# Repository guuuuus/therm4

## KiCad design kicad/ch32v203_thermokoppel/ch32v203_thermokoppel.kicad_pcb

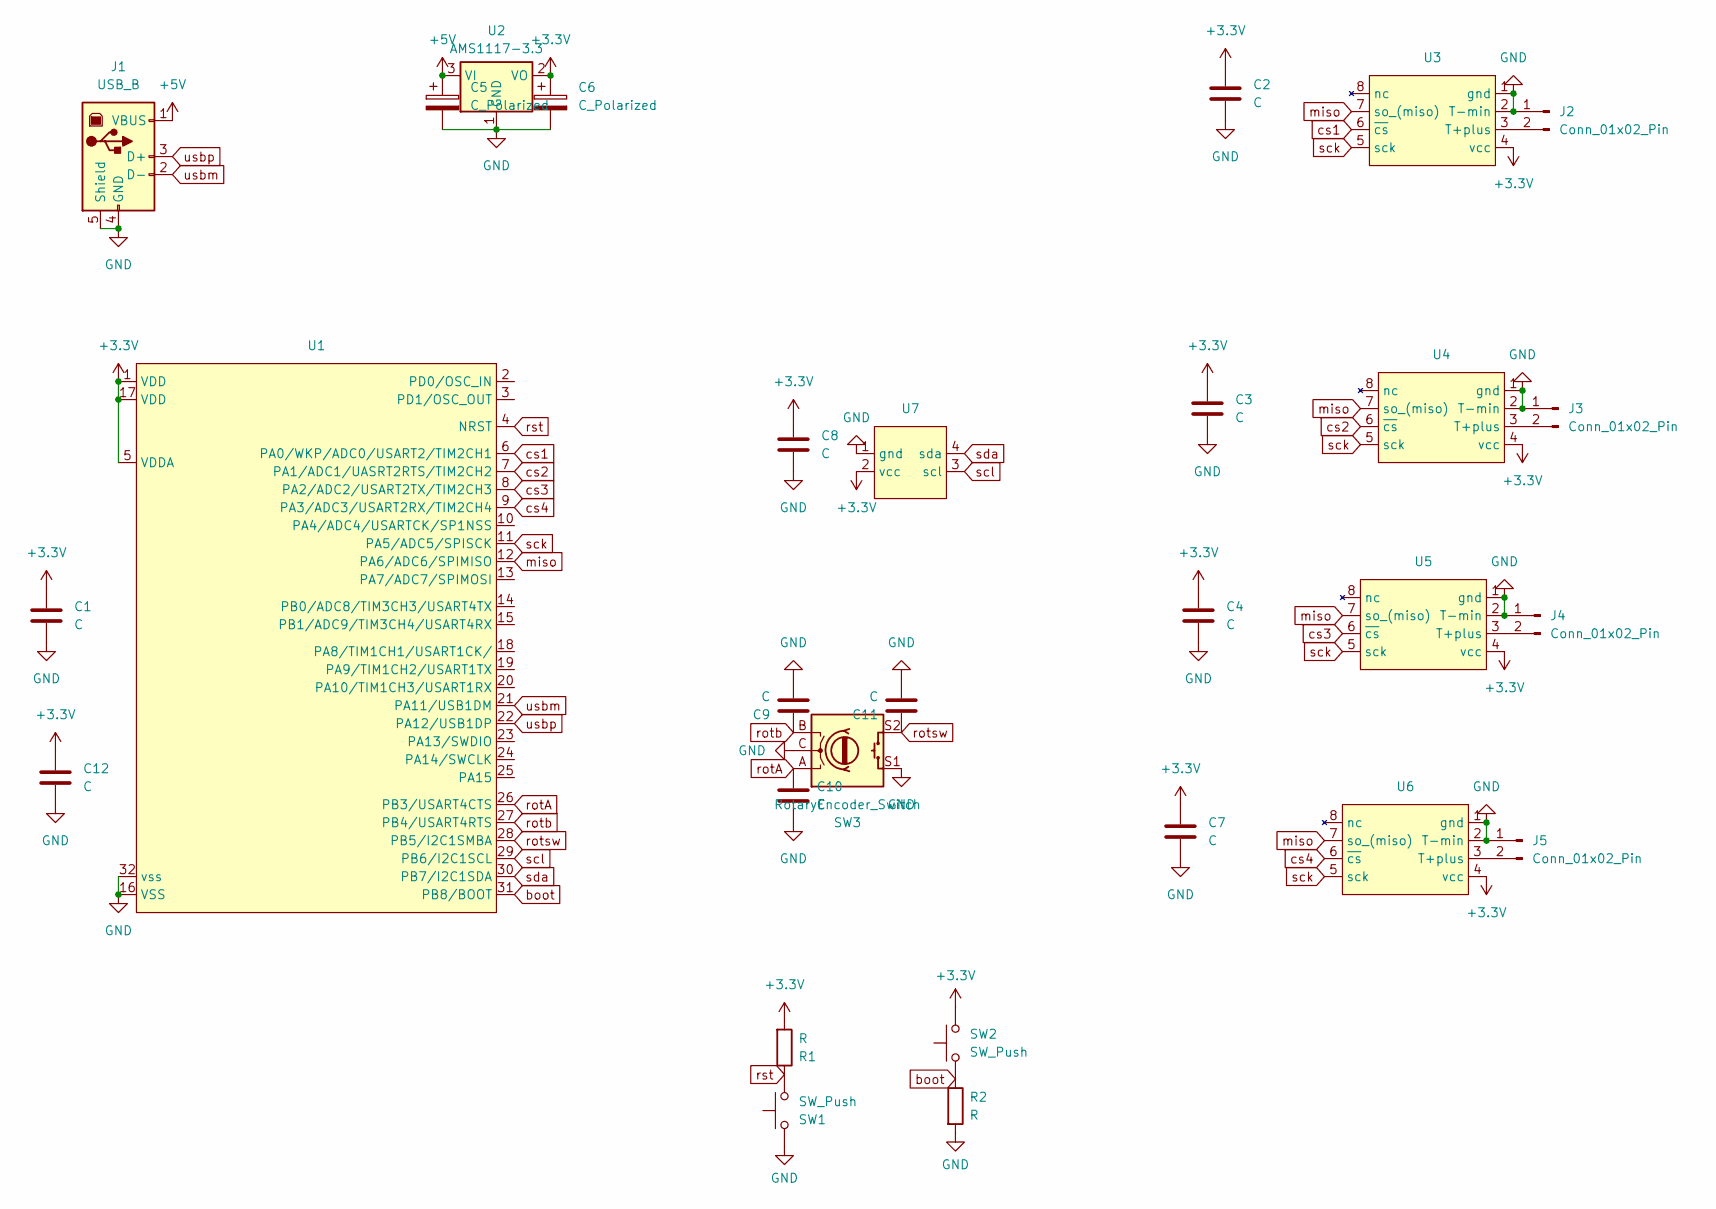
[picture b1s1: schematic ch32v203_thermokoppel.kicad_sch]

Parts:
C1, C2, C3, C4, C7, C8, C9, C10, C11, C12: C; C_1206_3216Metric_Pad1.33x1.80mm_HandSolder
C5, C6: C_Polarized; CP_Radial_D5.0mm_P2.00mm
J1: USB_B; usb_b_lumberg_ali
J2, J3, J4, J5: Conn_01x02_Pin; PhoenixContact_MCV_1,5_2-G-5.08_1x02_P5.08mm_Vertical
R1, R2: R; R_Axial_DIN0207_L6.3mm_D2.5mm_P7.62mm_Horizontal
SW1, SW2: SW_Push; SW_PUSH_6mm
SW3: RotaryEncoder_Switch; RotaryEncoder_Alps_EC11E-Switch_Vertical_H20mm_CircularMoun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
U1: LQFP-32_7x7mm_P0.8mm
U2: AMS1117-3.3; SOT-223-3_TabPin2
U3, U4, U5, U6: SO-8_5.3x6.2mm_P1.27mm
U7: 0_96_oled

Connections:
+3.3V: C1.1, C2.1, C3.1, C4.1, C6.1, C7.1, C8.1, C12.1, R1.2, SW2.2, U1.1 (VDD), U1.5 (VDDA), U1.17 (VDD), U2.2 (VO), U3.4 (vcc), U4.4 (vcc), U5.4 (vcc), U6.4 (vcc), U7.2 (vcc)
+5V: C5.1, J1.1 (VBUS), U2.3 (VI)
GND: C1.2, C2.2, C3.2, C4.2, C5.2, C6.2, C7.2, C8.2, C9.2, C10.2, C11.2, C12.2, J1.4 (GND), J1.5 (Shield), J2.1, J3.1, J4.1, J5.1, R2.2, SW1.2, SW3.C, SW3.S1, U1.16 (VSS), U1.32 (vss), U2.1 (GND), U3.1 (gnd), U3.2 (T-min), U4.1 (gnd), U4.2 (T-min), U5.1 (gnd), U5.2 (T-min), U6.1 (gnd), U6.2 (T-min), U7.1 (gnd)
unnamed: J2.2, U3.3 (T+plus)
unnamed: J3.2, U4.3 (T+plus)
unnamed: J4.2, U5.3 (T+plus)
unnamed: J5.2, U6.3 (T+plus)
boot: R2.1, SW2.1, U1.31 (PB8/BOOT)
cs1: U1.6 (PA0/WKP/ADC0/USART2/TIM2CH1), U3.6 (~cs)
cs2: U1.7 (PA1/ADC1/UASRT2RTS/TIM2CH2), U4.6 (~cs)
cs3: U1.8 (PA2/ADC2/USART2TX/TIM2CH3), U5.6 (~cs)
cs4: U1.9 (PA3/ADC3/USART2RX/TIM2CH4), U6.6 (~cs)
miso: U1.12 (PA6/ADC6/SPIMISO), U3.7 (so_(miso)), U4.7 (so_(miso)), U5.7 (so_(miso)), U6.7 (so_(miso))
rotA: C10.1, SW3.A, U1.26 (PB3/USART4CTS)
rotb: C9.1, SW3.B, U1.27 (PB4/USART4RTS)
rotsw: C11.1, SW3.S2, U1.28 (PB5/I2C1SMBA)
rst: R1.1, SW1.1, U1.4 (NRST)
sck: U1.11 (PA5/ADC5/SPISCK), U3.5 (sck), U4.5 (sck), U5.5 (sck), U6.5 (sck)
scl: U1.29 (PB6/I2C1SCL), U7.3 (scl)
sda: U1.30 (PB7/I2C1SDA), U7.4 (sda)
usbm: J1.2 (D-), U1.21 (PA11/USB1DM)
usbp: J1.3 (D+), U1.22 (PA12/USB1DP)

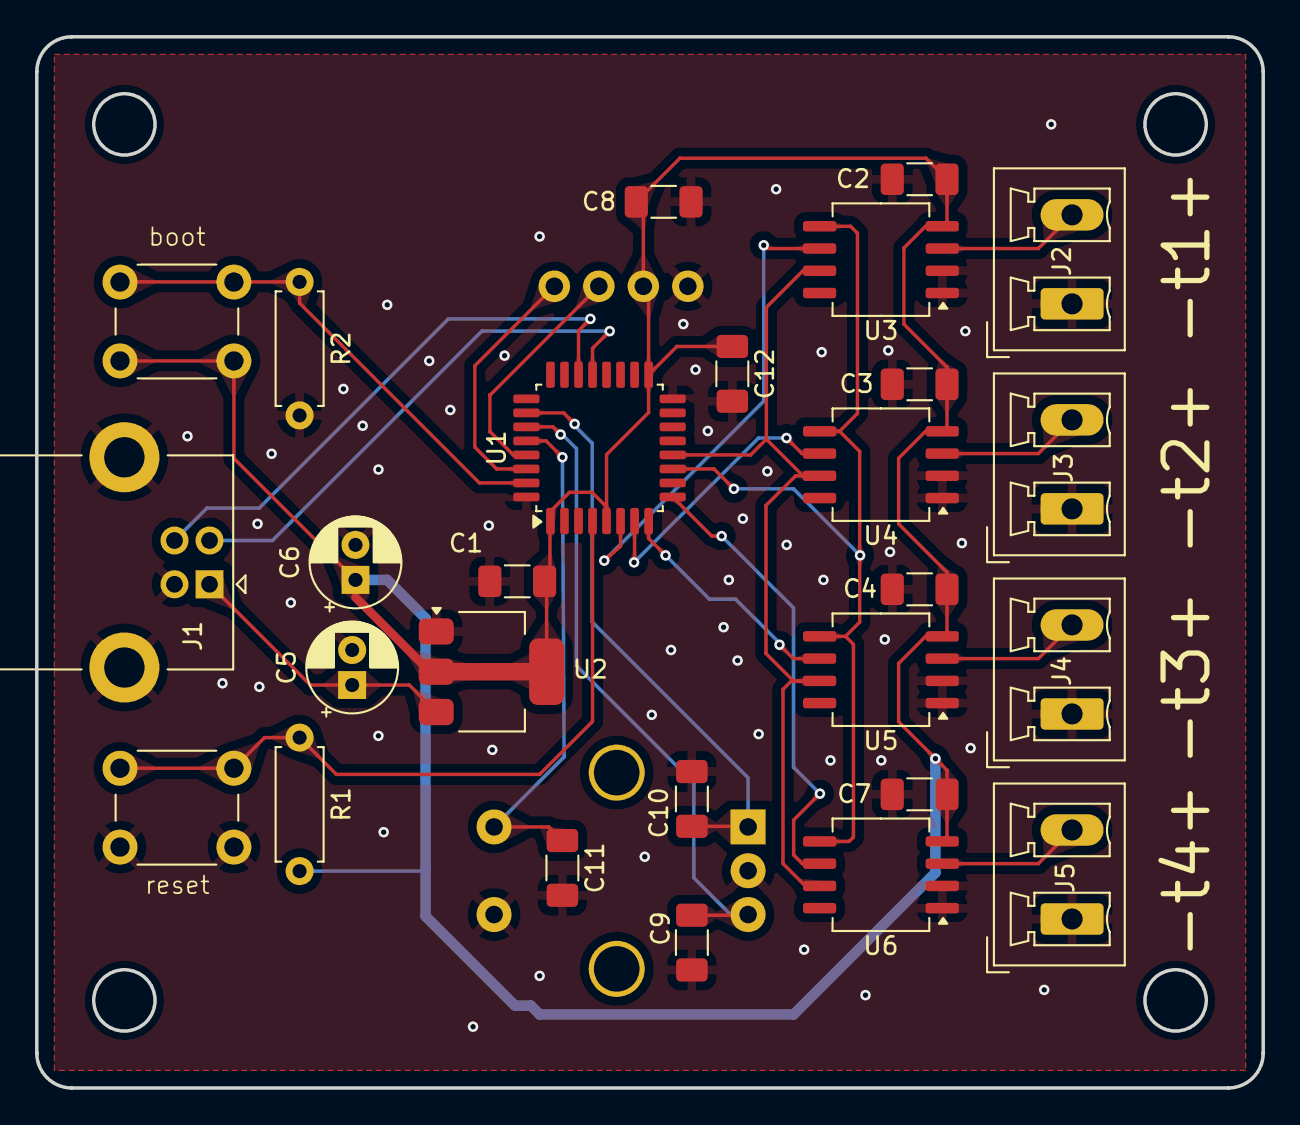
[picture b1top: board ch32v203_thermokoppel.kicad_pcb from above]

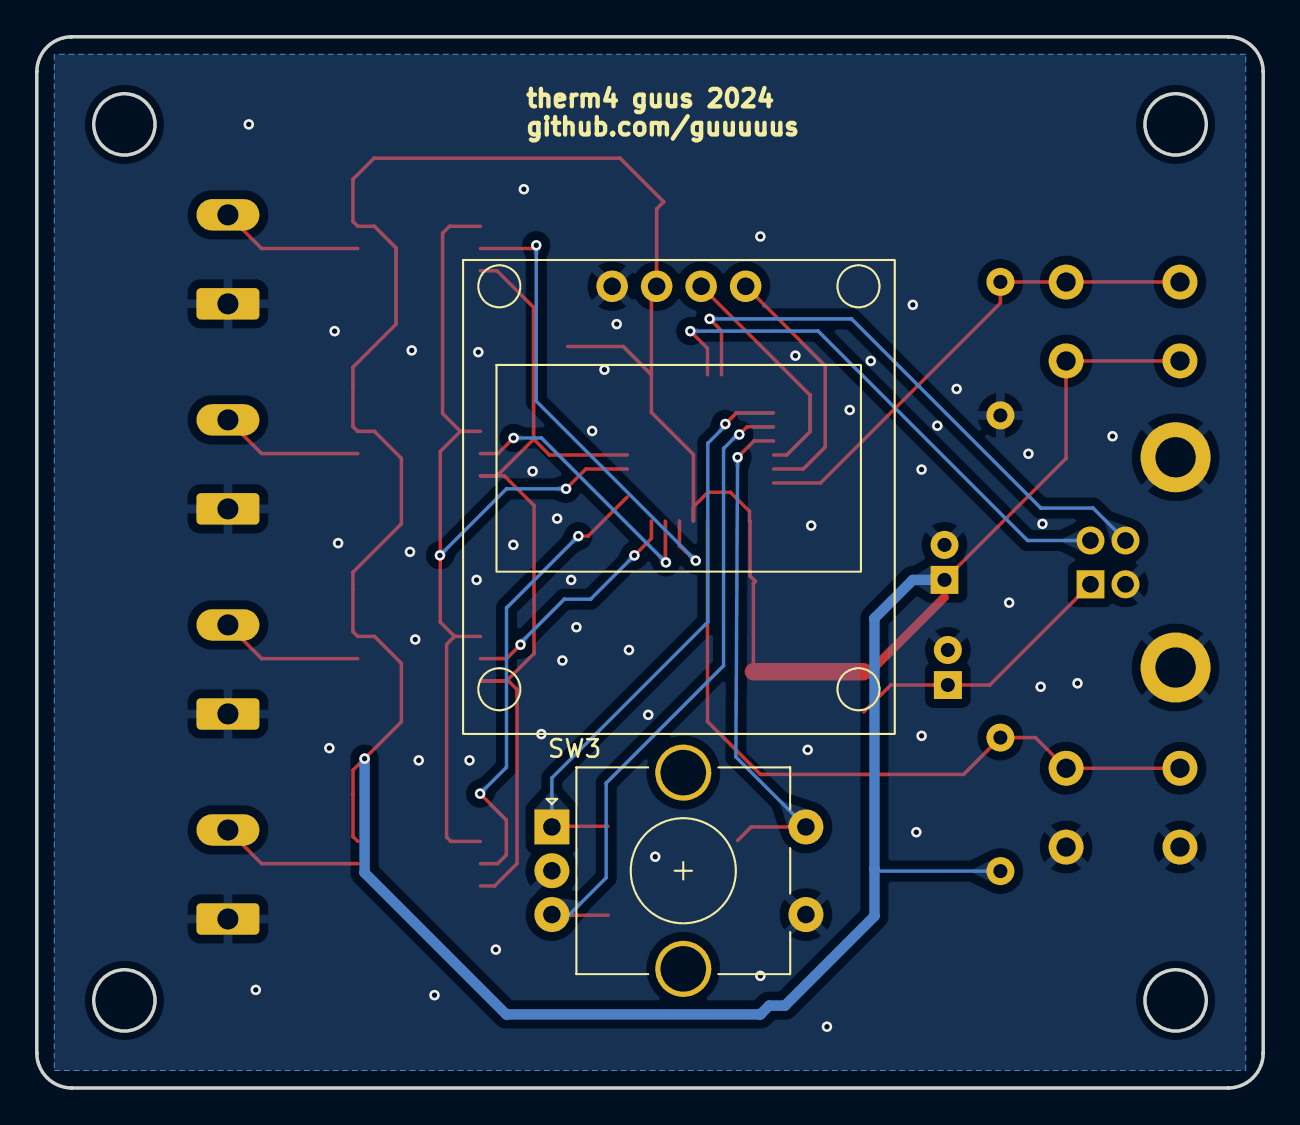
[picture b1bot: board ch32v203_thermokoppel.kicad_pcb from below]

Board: 2 copper layers, 70.0 x 60.0 mm, 29 parts (2 on the bottom side), 22 nets.
